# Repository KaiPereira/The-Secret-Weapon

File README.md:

# The Secret Weapon Information

You've been tasked with building the secret weapon, your goal is simple: Help build the largest collaborative PCB alongside 100 other highschoolers!

**Try to read all of this before adding something to the board, it's important information!**

First off, all the submissions will get 25 tickets, and 10% prototype progress! If you add something really, really cool, I might be able to hand out more tickets, but submit your component, before asking me!

Submission is as simple as this:

* Put your name down for what schematic sheet you're working on (so we don't have merge conflicts) in the canvas in #The-Secret-Weapon on Slack! If you don't want to be on Slack, you can probably work backwards in the sheets, like start at 100 or something!
* Fork/clone the repository
* Go into the schematic sheet you put yourself down for and rename it to your name + what you're working on!
* Wire up your component in the schematic (don't mess with other people's schematics without specific permission, unless they've added like an MCU or something), please don't add components that costs more than $5, so that we can get this thing made hopefully affordably!
* Route your component, make sure to have clean routing so that you don't take up too much space on the board! Also follow the routing guidelines that I listed in the PCB stackup information down below
* Commit the changes to your forked repository and open up a pull request!

I've added the root power system, it has 3 rails:

* 12V, 15A - Large components, high current/voltage, keep trace thick to high current stuff
* 5V, 4 - 5A - Medium currents, mid current/voltage, keep traces decently thick for mid current stuff
* 3V3. 1.5A - Low level systems, low current/voltage, don't use too much current on this layer

L3 is a 3V3 power fill, so you can just use a via to get down to it. If you need 5V or 12V, route it on the power layer, and then via up to use it!

The PCB stackup (how the layers are organized) is:

* TOP/SIGNAL  - Use this for routing!!! Put components on it too!
* GND - DON'T ROUTE ANYTHING ON THIS LAYER, if you need analog/split ground know what you're doing.
* PWR - Only route power stuff on this layer, and try to keep it clean
* SIGNAL - High speed routing if anyone wants, try to use the top and bottom and only use this if you need to
* GND - DON'T ROUTE ANYTHING ON THIS LAYER, if you need analog ground/split know what you're doing.
* BOTTOM/SIGNAL - Use this for routing!!! Don't put components on it though, but you're free to add silkscreen to it!

If any of your components need power or ground, you can just put a via down to either the ground or power layers. You can see how I did this with the TMC2209 stepstick driver I added in the very top left of the board!

Let's embrace the chaos, but try to make sure that whatever you're doing is actually wired/routed properly so we don't ruin the board for everyone else. When you make your PR, I might modify it a bit to work properly if I see something that's wrong, and it might also need to be re-routed if I'm behind on merging PR's! Also run DRC and check your part of the PCB, I'll also be fixing some of these if need be.

Try also not to add anything crazy big that takes up like a quarter for the board, or something that intentionally hoards power all the time, keep everyone else in mind with your components! Try to keep your components to like one big thing, and then you can add like decoupling, passives, etc. If there's no more I/O's left, you'll need to add an MCU, or wait for someone else to add one! Also try to add the manufacturer numbers, you can fine this under MFR.Part # on JLC/LCSC, for example https://jlcpcb.com/partdetail/471340-TMC2209LA/C465949 is TMC2209-LA!

Try not to move other people's pins around on the MCU's, or mess with the root systems unless you know what you're doing, some people need specific peripherals!

If you need any help, or to verify anything, feel free to put it in this channel and someone will definitely help!

Also feel free to customize your schematic sheet by adding text, and also add some cool silkscreen or drawings underneath your components.

**PLEASE KEEP ALL COMPONENTS TO THE TOP LAYER**, we want to make our board easily manufacturable and there's very few things that need components on both sides.

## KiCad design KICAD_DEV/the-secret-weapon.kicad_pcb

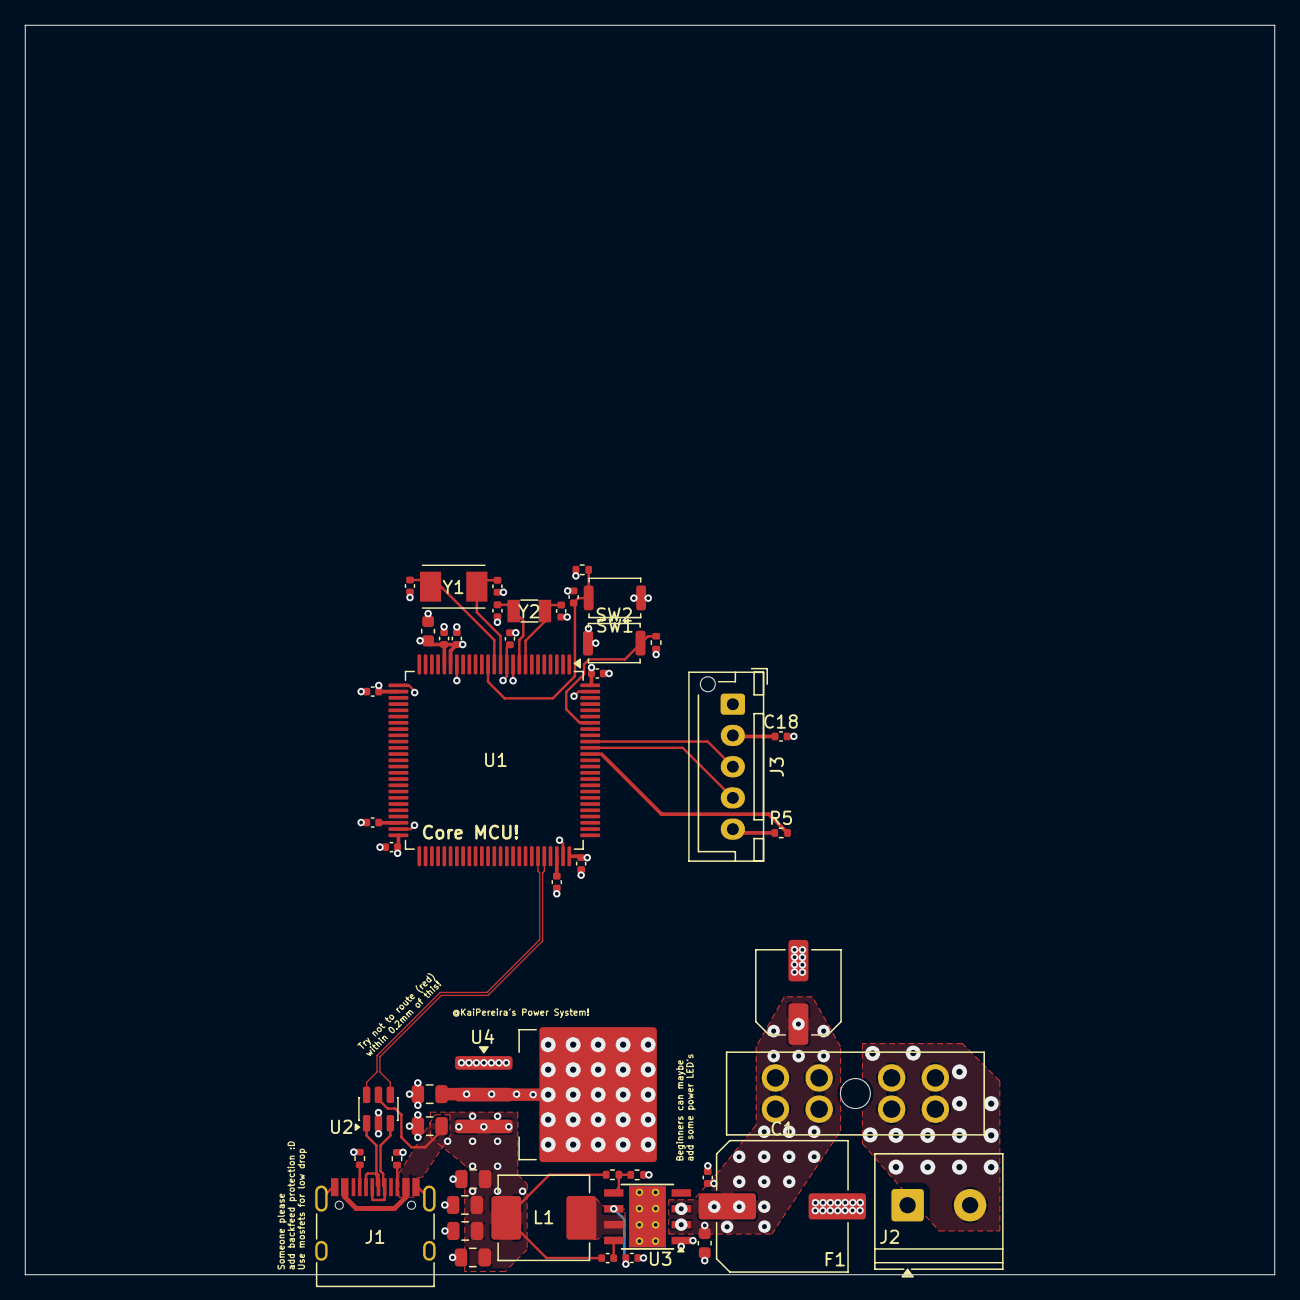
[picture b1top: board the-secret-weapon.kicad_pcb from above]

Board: 6 copper layers, 100.0 x 100.0 mm, 48 parts (0 on the bottom side), 27 nets.

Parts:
C1: 1000uF; C_Elec_10x10.2
C2: 220nF; C_0402_1005Metric
C3: 10uF; C_0603_1608Metric
C4, C10, C17, C18, C21, C23, C24, C25, C26, C27: 0.1uF; C_0402_1005Metric
C5, C6, C11, C12, C15: 22uF; C_0805_2012Metric
C7, C8: 2.2uF; C_0402_1005Metric
C9: 4.7uF; C_0603_1608Metric
C13: 1uF; C_0402_1005Metric
C14: 10uF; C_0805_2012Metric
C16: 100uF; C_Elec_6.3x5.8
C28, C29: 32pF; C_0402_1005Metric
C30, C31: 17pF; C_0402_1005Metric
F1: 20A; FuseHolder_Blade_ATO_Littelfuse_FLR_178.6165
J1: USB_C_Receptacle_USB2.0_14P; USB_C_Receptacle_HRO_TYPE-C-31-M-12
J2: Screw_Terminal_01x02; TerminalBlock_Phoenix_PT-1,5-2-5.0-H_1x02_P5.00mm_Horizontal
J3: Conn_01x05; JST_XH_B5B-XH-AM_1x05_P2.50mm_Vertical
L1: 6.8uH; L_TechFuse_SL0650
R1, R2: 5.1K; R_0402_1005Metric
R3: 100K; R_0402_1005Metric
R4: 24.9K; R_0402_1005Metric
R5: 1K; R_0402_1005Metric
R13, R14: 10K; R_0402_1005Metric
SW1, SW2: SW_Push; SW_Push_SPST_NO_Alps_SKRK
U1: STM32H743VITx; LQFP-100_14x14mm_P0.5mm
U2: USBLC6-2SC6; SOT-23-6
U3: LMR33640ADDA; Texas_HSOP-8-1EP_3.9x4.9mm_P1.27mm_ThermalVias
U4: LM1086S-3.3/TR; TO-263-3_TabPin2
Y1: 8 MHz; Crystal_SMD_TXC_7A-2Pin_5x3.2mm
Y2: 32.768 KHz; Crystal_SMD_3215-2Pin_3.2x1.5mm

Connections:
+3V3: C9.1, C10.1, C15.1, C17.1, C21.1, C23.1, C24.1, C25.1, C26.1, R13.1, SW2.1, U1.11 (VDD), U1.20 (VREF+), U1.21 (VDDA), U1.27 (VDD), U1.50 (VDD), U1.75 (VDD), U1.100 (VDD), U4.2 (VO)
+5V: C4.2, C5.1, C6.1, C11.1, C12.1, C14.1, C18.1, J1.A4 (VBUS), J1.A9 (VBUS), J1.B4 (VBUS), J1.B9 (VBUS), J3.2, L1.2, R3.1, U2.5 (VBUS), U4.3 (VI)
+12V: C1.1, C2.1, C3.1, C16.1, F1.2, U3.2 (VIN), U3.3 (EN)
BOOT: R14.1, SW2.2, U1.94 (BOOT0)
D+: U1.71 (PA12), U2.4 (I/O2)
D-: U1.70 (PA11), U2.6 (I/O1)
GND: C1.2, C2.2, C3.2, C5.2, C6.2, C7.2, C8.2, C9.2, C10.2, C11.2, C12.2, C13.2, C14.2, C15.2, C16.2, C17.2, C18.2, C21.2, C23.2, C24.2, C25.2, C26.2, C27.2, C28.2, C29.2, C30.2, C31.2, J1.A1 (GND), J1.A12 (GND), J1.B1 (GND), J1.B12 (GND), J1.S1 (SHIELD), J2.1, J3.1, R1.2, R2.2, R4.2, R14.2, SW1.1, U1.10 (VSS), U1.19 (VSSA), U1.26 (VSS), U1.49 (VSS), U1.74 (VSS), U1.99 (VSS), U2.2 (GND), U3.1 (GND), U3.9 (GND), U4.1 (GND)
unnamed: C7.1, U1.73 (VCAP)
unnamed: C8.1, U1.48 (VCAP)
unnamed: J1.A5 (CC1), R1.1
unnamed: J1.B5 (CC2), R2.1
unnamed: F1.1, J2.2
unnamed: J3.5, R5.1
unnamed: L1.1, U3.7 (BOOT)
unnamed: R3.2, R4.1, U3.5 (FB)
unnamed: C4.1, U3.8 (SW)
unnamed: C13.1, U3.6 (VCC)
OSC32_IN: C30.1, U1.8 (PC14), Y2.2
OSC32_OUT: C31.1, U1.9 (PC15), Y2.1
OSC_IN: C28.1, U1.12 (PH0), Y1.2
OSC_OUT: C29.1, U1.13 (PH1), Y1.1
RESET: C27.1, R13.2, SW1.2, U1.14 (NRST)
TFT_NRST: R5.2, U1.89 (PB3)
TFT_RX: J3.4, U1.90 (PB4)
TFT_TX: J3.3, U1.91 (PB5)
USB_D+: J1.A6 (D+), J1.B6 (D+), U2.3 (I/O2)
USB_D-: J1.A7 (D-), J1.B7 (D-), U2.1 (I/O1)

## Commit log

2025-10-22 init the PCB
2025-10-22 added README/JOURNAL
2025-10-22 removing duplicate PCB dev folder
2025-10-22 Add image to README.md
2025-10-22 Update README with project details and instructions
    Added introductory text about the collaborative PCB project.
2025-10-22 adding layer stackup of SIGNAL/GND/PWR/SIGNAL/GND/SIGNAL
2025-10-22 ground pour + core SoC STM32H757
2025-10-22 accidently used the wrong symbol
2025-10-24 working on USB PD
2025-10-24 adding my custom USB PD symbol
2025-10-24 revising my USB PD
2025-10-24 wiring USB-C
2025-10-25 starting to wire ESD
2025-10-25 more USB-C stuff
2025-10-25 finished wiring USB ESD protection
2025-10-25 starting to wire my USB PD
2025-10-25 more progress on USB PD
2025-10-26 almost done USB PD wiring (this is a lie)
2025-10-27 pretty much done USB-PD wiring, just gotta do GPIO's
2025-10-27 cooking
2025-10-28 some school shenanigans
2025-10-29 some decoupling and organization
2025-11-14 working on submission
2025-11-14 Not ready yet note
2025-11-14 changing the MCU for more chaos
2025-11-14 decoupling caps, vref, and vcap
2025-11-14 NRST and cleaner schematic
2025-11-14 more cleaning up and adding boot
2025-11-15 updating some stuff
2025-11-17 added the boot button
2025-11-17 adding the 8mhz crystal
2025-11-17 adding the 32.768KHz crystal!
2025-11-18 cleaning stuff up!
2025-11-18 switching to a PSU
2025-11-18 ESD Protection!
2025-11-18 some more progress
2025-11-19 working on the buck converter!
2025-11-19 finished buck converter wiring!
2025-11-19 added all the basic footprints!
2025-11-19 assigning more footprints!g
2025-11-19 all footprints are in!
2025-11-19 added in the 1.5A 3V3 LDO!
2025-11-19 cleaning up the schematic, adding some footnotes for contributors!
2025-11-19 starting the actual board!
2025-11-20 starting the layout of my power system!
2025-11-20 an absolutely gorgeous power layoutgit add .
2025-11-20 changing cap size, but it's probably not adequate
2025-11-20 heading to school!
2025-11-20 grounding and working on power, added the 100uF cap
2025-11-20 adding the power fills
2025-11-21 working on some more routing!
2025-11-21 finished routing the power!
2025-11-21 layed out the main SoC
2025-11-21 routed the SoC!
2025-11-21 finished power routing, just have to add the power rails now!
2025-11-21 adjusting the power fills and adding the power rails!
2025-11-21 forgot to wire USB data pairs, doing that now!
2025-11-21 added some more warnings around the board and routed the USB data pairs!
2025-11-21 done with the root PCBgit add .
2025-11-21 added all 150 hierarchial sheets!
2025-11-21 adding some instructions inside of the schematic!
2025-11-21 wired my TMC2209 :D
2025-11-21 wired the TMC2209 to my MCU, also more instructions on the schematic!
2025-11-22 layed out all the components
2025-11-22 working on routing my TMC2209 driver!
2025-11-22 finished routing my TMC2209 motor driver!
2025-11-23 Updating the readme :D
2025-11-23 More information!
2025-11-23 removing some files
2025-11-23 removing hidden obsidian folder
2025-11-24 testing
2025-11-24 starting on the bot
2025-11-24 adding the gitignore and env vars
2025-11-24 placeholder everything!
